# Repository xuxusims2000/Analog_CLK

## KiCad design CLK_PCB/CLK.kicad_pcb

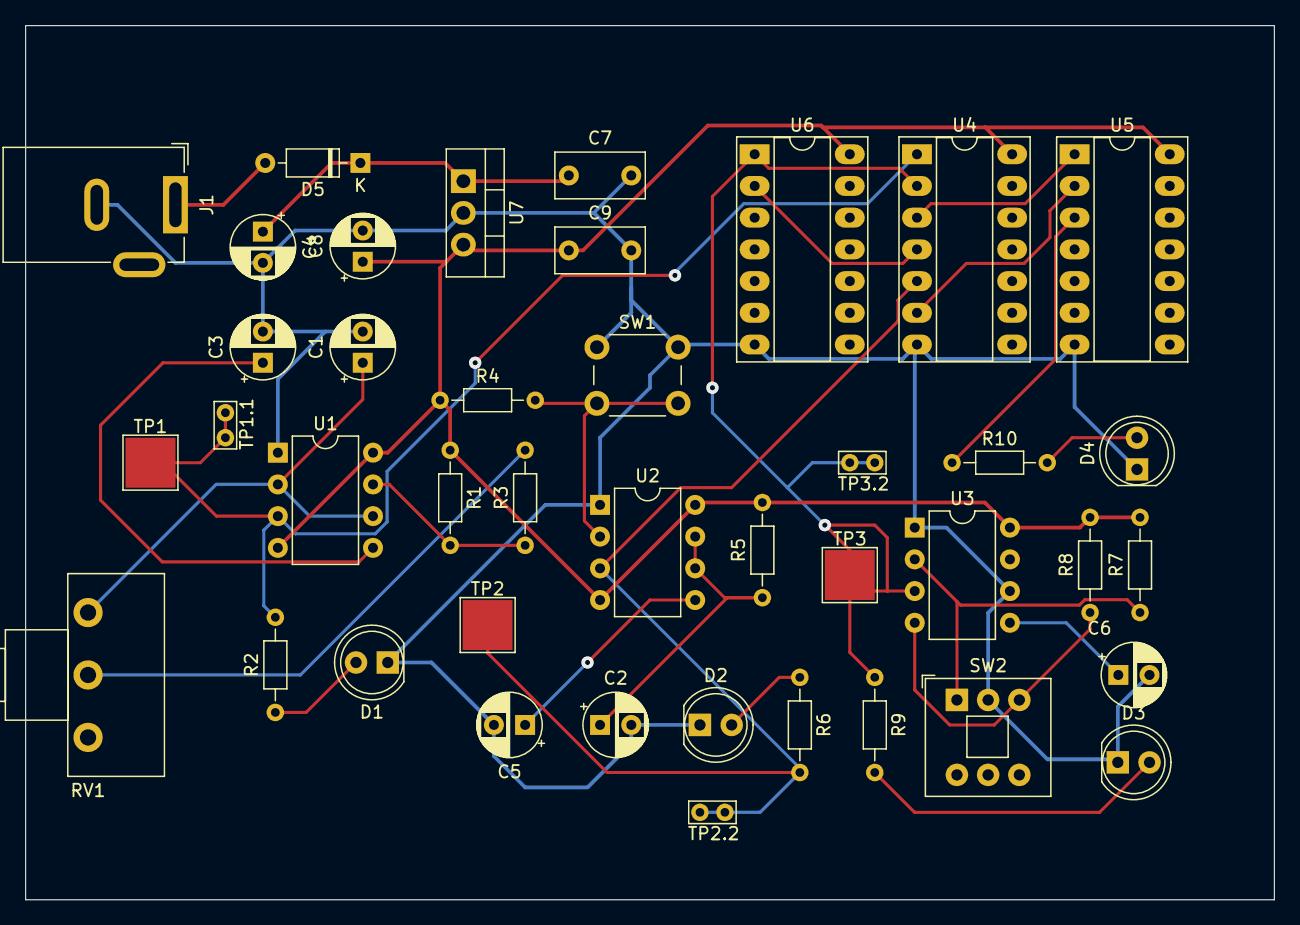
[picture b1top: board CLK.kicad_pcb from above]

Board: 2 copper layers, 100.0 x 70.0 mm, 41 parts (0 on the bottom side), 25 nets.

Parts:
C1: 1 uF; CP_Radial_D5.0mm_P2.50mm
C2: 10uF; CP_Radial_D5.0mm_P2.50mm
C3: op; CP_Radial_D5.0mm_P2.50mm
C4: 0.22 uF; CP_Radial_D5.0mm_P2.50mm
C5, C6: C; CP_Radial_D5.0mm_P2.50mm
C7, C9: 0.1 uF; C_Rect_L7.0mm_W3.5mm_P5.00mm
C8: 10 uF; CP_Radial_D5.0mm_P2.50mm
D1, D2, D3, D4: LED; LED_D5.0mm
D5: 1N6857; D_DO-35_SOD27_P7.62mm_Horizontal
J1: Jack-DC; BarrelJack_GCT_DCJ200-10-A_Horizontal
R1, R3, R4, R7, R8: 1k; R_Axial_DIN0204_L3.6mm_D1.6mm_P7.62mm_Horizontal
R2: R; R_Axial_DIN0204_L3.6mm_D1.6mm_P7.62mm_Horizontal
R5: 30k; R_Axial_DIN0204_L3.6mm_D1.6mm_P7.62mm_Horizontal
R6: 320; R_Axial_DIN0204_L3.6mm_D1.6mm_P7.62mm_Horizontal
R9, R10: 340; R_Axial_DIN0204_L3.6mm_D1.6mm_P7.62mm_Horizontal
RV1: R_Potentiometer 5k; Potentiometer_Piher_T-16H_Single_Horizontal
SW1: SW_DIP_x01; SW_PUSH_6mm_H5mm
SW2: SW_SPDT; SW_Push_2P2T_Toggle_CK_PVA2xxH2xxxxxxV2
TP1, TP2, TP3: TestPoint; TestPoint_Pad_4.0x4.0mm
TP1.1, TP2.2, TP3.2: TestPoint; TestPoint_Bridge_Pitch2.0mm_Drill0.7mm
U1, U2, U3: NE555P; DIP-8_W7.62mm
U4: 74LS08; DIP-14_W7.62mm_Socket_LongPads
U5: 74LS32; DIP-14_W7.62mm_Socket_LongPads
U6: 74LS04; DIP-14_W7.62mm_Socket_LongPads
U7: L7805; TO-220-3_Vertical

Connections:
CLK_OUT: R10.1, U5.3
GND: C1.2, C2.2, C3.2, C4.2, C5.2, C6.2, C7.2, C8.2, C9.2, D1.1 (K), D2.1 (K), D3.1 (K), D4.1 (K), J1.2, SW1.1, SW2.2 (B), U1.1 (GND), U2.1 (GND), U3.1 (GND), U3.6 (THR), U4.7 (GND), U5.7 (GND), U6.7 (GND), U7.2 (GND)
MUX1: R2.2, TP1.1, TP1.1.1, U1.3 (Q), U4.1
MUX2: R6.2, TP2.1, TP2.2.1, U2.3 (Q), U4.5
MUX3: R9.1, TP3.1, TP3.2.1, U3.3 (Q), U4.2, U6.1
unnamed: D1.2 (A), R2.1
unnamed: D2.2 (A), R6.1
unnamed: D3.2 (A), R9.2
unnamed: D4.2 (A), R10.2
unnamed: D5.2 (A), J1.1
unnamed: C4.1, C7.1, D5.1 (K), U7.1 (IN)
unnamed: R3.2, RV1.2
unnamed: R7.1, SW2.1 (A), U3.2 (TR)
unnamed: R8.1, SW2.3 (C), U3.4 (R)
unnamed: C3.1, U1.5 (CV)
unnamed: R1.2, R3.1, U1.7 (DIS)
unnamed: C1.1, RV1.1, U1.2 (TR), U1.6 (THR)
unnamed: C5.1, U2.5 (CV)
unnamed: C2.1, R5.1, U2.6 (THR), U2.7 (DIS)
unnamed: R4.2, SW1.2, U2.2 (TR)
unnamed: C6.1, U3.5 (CV)
unnamed: U4.3, U5.1
unnamed: U4.4, U6.2
unnamed: U4.6, U5.2
Vin: C8.1, C9.1, R1.1, R4.1, R5.2, R7.2, R8.2, U1.4 (R), U1.8 (VCC), U2.4 (R), U2.8 (VCC), U3.8 (VCC), U4.14 (VCC), U5.14 (VCC), U6.14 (VCC), U7.3 (OUT)

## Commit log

2024-10-18 primer commit projecte clk
2024-10-18 pujant fitxer prova
2024-10-18 fixer prova borrat
